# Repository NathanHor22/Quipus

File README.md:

# Quipus

Quipus records conversations with consent and turns them into a transcript,
meeting brief and follow-up tasks. Review proposed meetings in the dashboard
before sending Google Calendar invitations.

*Illustrative device render. The button diagram below defines the controls;
physical testing is still required for each new firmware build.*

[Open dashboard](https://quipus-sales-rep-assistant.vercel.app) ·
[Download firmware](https://github.com/NathanHor22/Quipus/actions/workflows/waveshare-firmware.yml) ·
[Full Waveshare guide](hardware/lantern-firmware/WAVESHARE.md) ·
[Developer setup](docs/configuration.md)

## Start with the recorder

This guide is for the **Waveshare ESP32-S3-LCD-1.54 non-touch board** with
16 MB flash and 8 MB PSRAM. Other supported boards need their own firmware.

1. Insert a **FAT32 microSD card** with the recorder powered off. Recording
   requires the card; setup and reports can work without it. Back up existing
   files before formatting a card. Quipus never formats cards automatically.
2. Connect USB-C power. For firmware **0.10.2**, open a successful
   [Waveshare firmware build](https://github.com/NathanHor22/Quipus/actions/workflows/waveshare-firmware.yml),
   download its `quipus-waveshare-lcd-154` artifact, extract it, then extract
   the firmware ZIP inside. Follow `README.txt` to flash all five images
   together. The manifest identifies the version, source commit and hashes.
3. In **Chrome on Windows or Android**, sign in at
   [Devices](https://quipus-sales-rep-assistant.vercel.app/dashboard/devices), choose
   **Connect with Bluetooth**, and select `Quipus-BT-XXXX`. Enter the LCD PIN
   if the operating system asks. Provide a **2.4 GHz Wi-Fi** network and choose
   **Save and connect**. Wait for this recorder to appear online in your account.
4. On **iPhone/Safari**, create a pairing code in Devices and use the
   [Wi-Fi setup fallback](hardware/lantern-firmware/WAVESHARE.md#wi-fi-fallback-and-recording-controls).
   Bluetooth is used for setup on supported browsers; recordings upload over Wi-Fi.
5. When the screen says **READY**, tap the **left button** to request recording.
   Ask everyone for consent and follow the spoken/display prompt. Confirm the
   screen says **RECORDING** before relying on capture.
6. Tap **left** again to stop. Keep the recorder powered while it saves and
   uploads. Open the conversation in the dashboard to check its audio,
   transcript and brief. Review any proposed meeting before approving an invite.

## Which button is which?

**Face the screen with its text upright and the three buttons ABOVE it**, as
in the device photos. In this orientation, the left button is PLUS, the middle
is PWR, and the right is BOOT. Turn the device around and left/right will reverse.

| Position | Tap and release | Hold |
| --- | --- | --- |
| **Left — PLUS** | Request consent/start recording; stop recording; interrupt a report | **1.2 s** while ready: play the daily report. During recording: stop. |
| **Middle — PWR** | **Volume down** | **2 s** while ready: power off/sleep. Pending private recordings block shutdown. |
| **Right — BOOT** | **Volume up** | During USB connection: enter the flashing bootloader. Leave released for normal startup. |
| **Left + right together** | — | **3 s**: clear Wi-Fi/pairing. Unsynced private recordings block reset. |

Volume taps require **0.10.2 or later**. Each tap changes volume by 10 points;
`V80` in the top bar means 80%. Zero mutes the speaker, and 100 is the configured
maximum. It starts at 80 after every restart. Volume affects prompts, reports,
chimes and replay, including during report playback; microphone gain and
recorded audio stay unchanged. Reset chords and long holds do not change volume.

The wake phrase is **Computer**, followed by a command. Follow the consent
prompt before recording. Daily reports need a working paired cloud connection.

## Battery

USB-C power works without a battery. For portable use, ask for the original
Waveshare **3.7 V 1000 mAh rechargeable lithium battery** for this exact model,
with an **MX1.25 2-pin connector**. Confirm pack dimensions and wire polarity
with the supplier; capacity and a similar-looking plug alone do not establish fit.
Install the supplied insulating sheet between the battery and PCB.

The default firmware does not estimate battery percentage. If you install a
battery, [enable the battery option and rebuild](hardware/lantern-firmware/WAVESHARE.md#build-and-flash)
to display the voltage-based estimate. Do not flash another board's image.

Sources: [Waveshare product](https://www.waveshare.com/esp32-s3-lcd-1.54.htm),
[hardware documentation](https://docs.waveshare.com/ESP32-S3-Touch-LCD-1.54),
[assembly guide](https://docs.waveshare.com/ESP32-S3-Touch-LCD-1.54/Instructions-For-Use).

## Develop and maintain

```sh
npm ci
npm run dev
```

Use Node.js 22. Local development without Supabase opens a fictional sample;
production authentication and provider setup are documented in
[configuration](docs/configuration.md) and [deployment](docs/deployment.md).

| Area | Source |
| --- | --- |
| Dashboard and server routes | `app/`, `components/`, `lib/` |
| Waveshare firmware and GPIO mapping | `hardware/lantern-firmware/` |
| Portable firmware tests | `scripts/test-firmware-boards.py` |
| Database migrations | `supabase/migrations/` |
| Recording worker | `recording-worker/` |
| System contracts | [ARCHITECTURE.md](ARCHITECTURE.md) |

```sh
python3 scripts/test-firmware-boards.py
python3 hardware/lantern-firmware/generate-setup-portal.py --check
npm run typecheck
npm test
npm run build
```

Firmware builds run in GitHub Actions using ESP-IDF 5.2.3. Compilation and
portable tests do not establish radio pairing, audible output or recording
reliability on a physical device. Before using a new build in a meeting,
check consent/start/stop, both volume buttons, a recording over 60 seconds,
its replay duration, and recovery after loss of Wi-Fi.

Waveshare support incorporates [jinchuntan/quipus](https://github.com/jinchuntan/quipus)
at `1d92ce5`, alongside this repository's existing firmware repairs.
See [integration notes](docs/upstream-sync.md) for provenance and validation.

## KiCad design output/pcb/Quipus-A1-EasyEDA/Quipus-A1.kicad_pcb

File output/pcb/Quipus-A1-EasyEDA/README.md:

# Quipus A1 — physical EasyEDA import carrier

This directory defines the physical footprints and placement used to build the custom Quipus recorder PCB. The import package is in `output/pcb/Quipus-A1-EasyEDA/`; its principal files are `Quipus-A1.kicad_sch` and `Quipus-A1.kicad_pcb`. The native EasyEDA design must be checked after importing those files.

The carrier has a 65 × 105 mm, 1.6 mm thick, four-layer board, 144 electrical components, 92 canonical nets and four additional mounting-hole footprints. Its 31 distinct physical packages are included in `Quipus.pretty/`. The front includes a non-electrical screen-envelope guide and the user buttons. Rear connectors include the battery, speaker, digital-microphone expansion and microSD socket. USB-C is at the bottom; the card socket opens toward the right side when viewed from the front. Both embedded microphone packages are mounted on the rear and receive sound through actual 0.60 mm non-plated board holes.

## Files and authority

| File | Purpose |
| --- | --- |
| `footprints-power.json`, `footprints-controller.json`, `footprints-audio.json` | Per-reference physical package, physical pad mapping, source and footprint SHA-256 |
| `placement.json` | Applied component position, rotation, face and mechanical envelopes; parent-owned |
| `kicad_format.py` | Conversion of physical footprint geometry into the legacy PCB import format |
| `build_import.py` | Builds the PCB, flat self-contained schematic, footprint library, CSVs and ZIP from the canonical source netlist |
| `validate_footprints.py` | Independent source-net/pin coverage, footprint pad numbering and checksum checks |
| `validate_import.py` | Independent final-carrier electrical associations and geometry-conversion audit |
| `validate_placement.py` | Independent actual-board physical placement audit |
| `render_placement.py` | Renders actual PCB pads, drilled holes, fabrication outlines, board edge and keepouts into a labelled front/rear PNG |
| `mic-placement-patch.json` | A four-part lower-microphone proposal against a recorded board hash; generating it does not change the PCB itself |

The circuit JSONs and `output/pcb/Quipus-A1/connections.json` establish electrical connections. A placement change does not alter their pin numbers or nets. The generated board is the authority for the preview; its SHA-256 appears in the preview and validation reports. Rear preview geometry is mirrored so it is a component-side view. The screen rectangle is a mounting guide for an off-board display, not an invented populated PCB component.

## Local checks

Run from the repository root with Python. Pillow is needed only for the PNG renderer.

```powershell
python hardware/quipus-pcb/rev-a/easyeda/validate_footprints.py
python hardware/quipus-pcb/rev-a/easyeda/build_import.py
python hardware/quipus-pcb/rev-a/easyeda/validate_import.py
python hardware/quipus-pcb/rev-a/easyeda/validate_placement.py
python hardware/quipus-pcb/rev-a/easyeda/render_placement.py
```

`build_import.py` rewrites generated import outputs using the current applied `placement.json`. It does not apply a proposal file. The independent audits and preview must be rerun after rebuilding, and the import ZIP must be refreshed after any file included in it changes.

The footprint audit checks the exact pad numbers against each circuit reference, including shared/repeated copper pads and unnumbered mechanical pads. The carrier audit compares the final schematic and PCB with canonical source pins/nets, checks every imported copper pad and graphic primitive, and tests the microphone annuli/paste, exposed pads, SD detector contacts and RF keepouts. The placement audit uses actual stitched courtyard polygons; it also checks front/back plated-through-hole interference, copper-to-edge clearance, mounting-head space, screen interference, connector direction and RF component exclusion on all four copper layers. Pad outlines in the geometric placement test use conservative rotated rectangles; circular mounting keepouts use 48-segment polygons.

Read `output/pcb/Quipus-A1-EasyEDA/import-validation.json` and `placement-validation.json` in this directory for the latest board hash and check results. Local checks do not exercise the native EasyEDA importer or native CAD rule engines.

## Verification status

| Stage | Status |
| --- | --- |
| Physical package/pad mapping and source comparison | Locally audited; details in the three footprint-review documents and `footprint-crosscheck.md` |
| Final carrier pin/net association and converted geometry | Local audit available in `import-validation.json` |
| Applied PCB physical placement | Local audit available in `placement-validation.json` |
| Native EasyEDA import and comparison of rendered package geometry | Imported; corrected microphone ground annuli accepted and saved in the native library, refreshed on U20/U21, with all eight quarter pads connected to GND |
| Native EasyEDA electrical-rule check (ERC) | Nine organized A3 schematic pages: 0 fatal findings, 0 errors, 0 warnings, 9 informational findings |
| Copper routing and ground pours | **Not complete** |
| Native PCB design-rule check (DRC) | Final native run: 451 unrouted connection findings, one schematic import metadata mismatch, **0 clearance findings**; routing remains incomplete |
| Fabrication release | **Not approved; this is an unrouted engineering carrier** |

Native cloud project: **Quipus A1 – Hardware Rev A**, ID `522f339b1e454ea3a6b4b8e11788511f`, PCB document `52caa9452ee66dee`; review date 1 October 2026. The nine schematic pages are ordered by function: USB-C/charger, USB current/suspend, power switch/always-on supply, main regulator, fuel gauge, processor/display/SD, controller support, buttons/service, and microphones/speaker. Native page sources retain all 144 references, 92 nets and 471 symbol pins. The final schematic-to-PCB import preview filtered for net changes contains no rows; the preview was cancelled because device metadata and the four PCB-only mounting holes still need deliberate synchronization. Evidence is in `native/`. A successful local audit or a visually plausible placement is not a routing or manufacturing sign-off.

The generated KiCad carrier and its ZIP do **not** incorporate the separate native microphone correction. Future reimports must preserve or reapply `native/microphone-footprint-final.esource` and verify all four pad-5 ground quarters on each microphone. The accepted native source checksum and native DRC evidence are separate from the generated-carrier checksum.

The current CAD-derived PNG and local placement report refer to PCB SHA-256 `5f48361c2ff1a57b59c6621943f8e72196b9cb33372bc079969b886fc56f1d6c`. Its top and bottom microphone ports are at (5.75,9.49) and (59.25,92.29) mm respectively. The lower bypass/series group has been applied; proposal files remain a record of the earlier geometry check, not the authority for the generated board. All 65 revised component positions/rotations/faces were also checked in native PCB Properties. The layout places charger/current-limit parts together on the lower front, the battery connectors toward the rear left, and the compact converter/distribution group on the lower rear. These groupings aid subsequent routing; zero placement collisions do not prove signal integrity or thermal performance.

## Specific native and assembly checks

After import, inspect the two Infineon microphone land patterns at high zoom: pin 5 is a copper annulus with an empty centre, the sound aperture is 0.60 mm NPTH, and its three paste sectors must remain separate. The native annulus uses four touching polygon pads, all numbered 5 and all assigned GND. Confirm the ESP32-S3 antenna notch and RF exclusion remain on all four copper layers; compare all USB-C shared contacts, the BQ27441 exposed-pad geometry, the MAX98357A exposed pad and the Hirose card detector pads against the source footprint files. Then use the actual native rules and the PCB fabricator's published tolerances for routing and final checks.

The microphone copper-to-sound-hole edge separation is 0.1925 mm and needs confirmation with the intended fabricator. Microphone stencil apertures and acoustic hole cleanliness need assembler review. The case must preserve both acoustic paths and microSD insertion/ejection clearance, and it must leave USB-C accessible. An external LiPo pouch, case rib or speaker chamber must not cover a microphone sound port. Do not fabricate from the preview image; fabrication output must come from the completed, checked native board.

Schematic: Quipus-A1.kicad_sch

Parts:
C1: 4.7uF 16V X7R; C_0805_2012Metric
C2, C16: 10uF 10V X7R; C_0805_2012Metric
C3, C17, C18: 22uF 10V X7R; C_0805_2012Metric
C4, C7, C8, C9, C10, C11, C12, C19: 100nF 10V; C_0603_1608Metric
C5, C6, C14, C20: 1uF 10V X7R; C_0603_1608Metric
C13: 1uF 10V lowleakage X7R; C_0805_2012Metric
C15: 10nF 25V X7R; C_0603_1608Metric
C21: 470nF 6.3V X7R; C_0603_1608Metric
C200, C202: 1uF X7R 10V; C_0603_1608Metric
C201, C203, C205: 100nF X7R 10V; C_0603_1608Metric
C204: 4.7uF X7R 10V; C_0603_1608Metric
C206: 10uF X7R 10V; C_0805_2012Metric
C207: 47uF X7R 10V DNP; C_1210_3225Metric; not fitted
C300: 1uF; C_0603_1608Metric
C301, C305, C310: 10uF; C_0603_1608Metric
C302, C306, C311, C320, C321, C330, C340: 100nF; C_0603_1608Metric
C303, C304: DNP / C0G tuning footprint; C_0603_1608Metric; not fitted
C312, C331, C332, C333, C334: 10nF; C_0603_1608Metric
D1: TPD1E10B06DYAR; Quipus_TI_DYA0002A_TPD1E10B06
F1: Littelfuse 0467002.NRHF 2 A; Fuse_0603_1608Metric
J1: GCT USB4105-GF-A; Quipus_GCT_USB4105_GF_A_SHARED_CONTACTS
J2: JST S2B-PH-SM4-TB(LF)(SN) battery; JST_PH_S2B-PH-SM4-TB_1x02-1MP_P2.00mm_Horizontal
J3: 3-pin keyed NTC connector - JST SH family candida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; JST_SH_SM03B-SRSS-TB_1x03-1MP_P1.00mm_Horizontal
J4: SM04B-SRSS-TB; JST_SH_SM04B-SRSS-TB_1x04-1MP_P1.00mm_Horizontal
J5: SM02B-SRSS-TB; JST_SH_SM02B-SRSS-TB_1x02-1MP_P1.00mm_Horizontal
J6: DM3AT-SF-PEJM5; Quipus_Hirose_DM3AT-SF-PEJM5_AB
J7: B8B-PH-K-S(LF)(SN); JST_PH_B8B-PH-K_1x08_P2.00mm_Vertical
L1: 0.47uH Coilcraft XFL4015-471ME; Quipus_Coilcraft_XFL4015
R1: 1.24k 1%; R_0603_1608Metric
R2: 2.00k 1%; R_0603_1608Metric
R3: 68.0k 1%; R_0603_1608Metric
R4, R5, R8, R9, R10, R11, R12, R14, R18, R316: 100k; R_0603_1608Metric
R6: 887k 1%; R_0603_1608Metric
R7, R13, R20, R21, R22, R25, R300, R301, R304, R305, R310, R311, R312, R313, R314, R321: 10k; R_0603_1608Metric
R15: 100ohm; R_0603_1608Metric
R16: 511k 1%; R_0603_1608Metric
R17: 91.0k 1%; R_0603_1608Metric
R19: 0.010ohm 1% lowTCR 0.25W; R_0805_2012Metric
R23, R24, R26: 1M; R_0603_1608Metric
R201, R202: 100 ohm 1%; R_0603_1608Metric
R203, R205, R207, R210, R211: 33 ohm 1%; R_0603_1608Metric
R204: 0 ohm; R_0603_1608Metric
R206, R208, R209: 100k 1%; R_0603_1608Metric
R302, R303, R315: 22ohm; R_0603_1608Metric
R306, R307: 33ohm; R_0603_1608Metric
R320: 330ohm; R_0603_1608Metric
R330, R331, R332, R333: 47k; R_0603_1608Metric
R341, R342: 49.9ohm; R_0603_1608Metric
SW1: POWER momentary normally-open; SW_SPST_B3U-1000P
SW300, SW301, SW302, SW303, SW304, SW305: B3U-1000P; Quipus_Omron_B3U-1000P
U1: ESP32-S3-WROOM-1-N16R8; ESP32-S3-WROOM-1
U2: BQ24074RGTR; Quipus_TI_RGT0016C_BQ24074
U3: TUSB320LAIRWBR; Quipus_TI_RWB0012A_TUSB320LAI
U4: TLV75533PDBVR; SOT-23-5
U5: SN74LVC1G04DBVR; SOT-23-5
U6: SN74LVC1G08DBVR; SOT-23-5
U7, U8: SN74LVC1G32DBVR; SOT-23-5
U9: LTC2951ITS8-1#TRPBF; TSOT-23-8
U10: TPS22918DBVR; SOT-23-6
U11: TPS63802DLAR; Quipus_TI_DLA0010A_TPS63802
U12: BQ27441DRZR-G1A; Quipus_TI_DRZ0012A_BQ27441
U13, U35: TPD2EUSB30DRTR; Texas_DRT-3
U20, U21: IM69D128SV01XTMA1; Infineon_IM69D128SV01_PG-TLGA-5-2_2.65x3.50mm_NPTH0.60
U22: MAX98357AETE+; MAX98357AETE_T1633-4_3x3mm_P0.5_EP1.23_90-0031C
U30: RV-3028-C7-TA-QC; MicroCrystal_C7_SON-8_1.5x3.2mm_P0.9mm
U31: PCA9536DR; SOIC-8_3.9x4.9mm_P1.27mm
U34: TS3USB221ARSER; Texas_UQFN-10_1.5x2mm_P0.5mm

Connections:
3V3_AON: C4.1, C6.1, C7.1, C8.1, C9.1, C10.1, R7.2, U3.12 (VDD), U4.5 (OUT), U5.5 (VCC), U6.5 (VCC), U7.5 (VCC), U8.5 (VCC)
3V3_FB: R16.2, R17.1, U11.4 (FB)
3V3_PG: R18.1, U11.5 (PG)
3V3_SYS: C17.1, C18.1, C19.1, C301.1, C302.1, C305.1, C306.1, C310.1, C311.1, C320.1, C330.1, C340.1, J6.4 (VDD), J7.8 (VCC), R4.2, R5.2, R13.2, R14.2, R16.1, R18.2, R21.2, R22.2, R25.2, R204.1, R300.1, R301.1, R304.1, R305.1, R310.1, R311.1, R312.1, R313.1, R314.1, R316.1, R330.1, R331.1, R332.1, R333.1, U1.2 (3V3), U11.6 (VOUT), U30.7 (VDD), U31.8 (VCC), U34.10 (VCC)
AMP_ENABLE: R209.1, U1.10 (GPIO17), U22.4 (SD_MODE)
AMP_GAIN: R208.2, U22.2 (GAIN_SLOT)
BAT_NTC: J3.1 (NTC), U2.1 (TS)
BAT_P: C2.1, R19.2, R320.1, U2.2 (BAT), U2.3 (BAT), U12.7 (SRN)
BAT_PACK_P: C20.1, J2.1 (PACK+), R19.1, U12.6 (BAT), U12.8 (SRP)
BOOT_N: R301.2, SW300.1 (A), U1.27 (GPIO0)
BTN_DOWN_N: C334.1, R333.2, SW304.1 (A), U31.5 (P3)
BTN_START_N: C331.1, R330.2, SW301.1 (A), U1.7 (GPIO7)
BTN_STOP_N: C332.1, R331.2, SW302.1 (A), U31.2 (P1)
BTN_UP_N: C333.1, R332.2, SW303.1 (A), U31.3 (P2)
BUCK_L1: L1.1, U11.9 (L1)
BUCK_L2: L1.2, U11.7 (L2)
CC_DEFAULT_NHIGH: R7.1, U3.7 (OUT1), U5.2 (A), U6.2 (B)
CHARGING_N: R4.1, U1.24 (GPIO47), U2.9 (CHG_N)
CHG_EN1: R10.1, U2.6 (EN1), U7.4 (Y)
CHG_EN2: R11.1, U2.5 (EN2), U8.4 (Y)
CHG_ILIM: R1.1, U2.12 (ILIM)
CHG_ISET: R2.1, U2.16 (ISET)
CHG_TMR: R3.1, U2.14 (TMR)
ESP_EN: C300.1, R300.2, SW305.1 (A), U1.3 (EN)
ESP_USB_DM: C303.1, R302.2, U1.13 (GPIO19_USB_D-)
ESP_USB_DP: C304.1, R303.2, U1.14 (GPIO20_USB_D+)
GAUGE_1V8: C21.1, U12.5 (VDD)
GAUGE_BIN: R20.1, U12.10 (BIN)
GAUGE_INT_N: R25.1, R26.1, U12.12 (GPOUT)
GND: C1.2, C2.2, C3.2, C4.2, C5.2, C6.2, C7.2, C8.2, C9.2, C10.2, C11.2, C12.2, C13.2, C14.2, C15.2, C16.2, C17.2, C18.2, C19.2, C20.2, C21.2, C200.2, C201.2, C202.2, C203.2, C204.2, C205.2, C206.2, C207.2, C300.2, C301.2, C302.2, C303.2, C304.2, C305.2, C306.2, C310.2, C311.2, C312.2, C320.2, C321.2, C330.2, C331.2, C332.2, C333.2, C334.2, C340.2, D1.2 (RETURN), J1.A1_B12 (GND), J1.B1_A12 (GND), J1.SH1 (SHIELD), J1.SH2 (SHIELD), J1.SH3 (SHIELD), J1.SH4 (SHIELD), J2.2 (PACK-), J3.2 (NTC_RETURN), J4.2 (GND), J6.6 (VSS), J6.B (CARD_DETECT_B), J6.SH (SHIELD), J7.7 (GND), R1.2, R2.2, R3.2, R8.2, R9.2, R10.2, R11.2, R17.2, R20.2, R23.2, R24.2, R26.2, R206.2, R209.2, R321.2, R341.2, R342.2, SW1.2, SW300.2 (B), SW301.2 (B), SW302.2 (B), SW303.2 (B), SW304.2 (B), SW305.2 (B), U1.1 (GND), U1.40 (GND), U1.41 (GND_EP), U2.4 (CE_N), U2.8 (VSS), U2.17 (EP), U3.3 (PORT), U3.10 (GND), U3.11 (EN_N), U4.2 (GND), U5.3 (GND), U6.3 (GND), U7.3 (GND), U8.3 (GND), U9.4 (GND), U10.2 (GND), U11.2 (MODE), U11.3 (AGND), U11.8 (GND), U12.3 (VSS), U12.13 (EP), U13.3 (GND), U20.4 (LR), U20.5 (GND), U21.5 (GND), U22.3 (GND), U22.11 (GND), U22.15 (GND), U22.17 (EP), U30.5 (VSS), U31.4 (GND), U34.5 (GND), U34.6 (OE_N), U34.9 (S), U35.3 (GND)
I2C_SCL: R22.1, R24.1, U1.17 (GPIO9), U12.2 (SCL), U30.3 (SCL), U31.6 (SCL)
I2C_SDA: R21.1, R23.1, U1.12 (GPIO8), U12.1 (SDA), U30.4 (SDA), U31.7 (SDA)
I2S1_BCLK: R211.1, U1.22 (GPIO14)
I2S1_BCLK_IC: R211.2, U22.16 (BCLK)
I2S1_DOUT: R207.1, U1.9 (GPIO16)
I2S1_DOUT_IC: R207.2, U22.1 (DIN)
I2S1_WS: R210.1, U1.8 (GPIO15)
I2S1_WS_IC: R210.2, U22.14 (LRCLK)
LCD_BL: J7.1 (BL), U1.21 (GPIO13)
LCD_CS_N: J7.4 (CS), R304.2, U1.18 (GPIO10)
LCD_DC: J7.3 (DC), U1.37 (GPIO43_U0TXD)
LCD_MOSI: J7.6 (DIN), R307.2
LCD_MOSI_MCU: R307.1, U1.19 (GPIO11)
LCD_RST_N: J7.2 (RST), R305.2, U1.36 (GPIO44_U0RXD)
LCD_SCLK: J7.5 (CLK), R306.2
LCD_SCLK_MCU: R306.1, U1.20 (GPIO12)
MAIN_RAW: C16.1, C205.1, C206.1, C207.1, R15.2, R208.1, U10.6 (VOUT), U11.1 (EN), U11.10 (VIN), U22.7 (VDD), U22.8 (VDD)
MIC_3V3: C200.1, C201.1, C202.1, C203.1, C204.1, J4.1 (3V3), R204.2, U20.1 (VDD), U21.1 (VDD), U21.4 (LR)
PDM_CLK: R203.1, R205.1, U1.4 (GPIO4)
PDM_CLK_EXT: J4.3 (CLK), R205.2
PDM_CLK_LOCAL: R203.2, U20.2 (CLOCK), U21.2 (CLOCK)
PDM_DIN0: R201.2, R202.2, U1.5 (GPIO5)
PDM_DIN1: J4.4 (DATA), R206.1, U1.6 (GPIO6)
POWER_HOLD: R14.1, U1.23 (GPIO21), U9.8 (KILL)
PWR_BUTTON_N: SW1.1, U9.2 (PB_N)
PWR_INT_N: R13.1, U1.11 (GPIO18), U9.5 (INT_N)
PWR_KILLT: C13.1, U9.3 (KILLT)
PWR_OFFT: C12.1, U9.7 (OFFT)
RTC_EVI: R321.1, U30.8 (EVI)
RTC_VBACKUP: C321.1, R320.2, U30.6 (VBACKUP)
SD_CD_N: C312.1, J6.A (CARD_DETECT_A), R316.2, U1.34 (GPIO41)
SD_CLK: J6.5 (CLK), R315.2
SD_CLK_MCU: R315.1, U1.31 (GPIO38)
SD_CMD: J6.3 (CMD), R310.2, U1.32 (GPIO39)
SD_D0: J6.7 (DAT0), R311.2, U1.33 (GPIO40)
SD_D1_PU: J6.8 (DAT1), R312.2
SD_D2_PU: J6.1 (DAT2), R313.2
SD_D3_PU: J6.2 (CD_DAT3), R314.2
SPK_N: J5.2 (SPK-), U22.10 (OUTN)
SPK_P: J5.1 (SPK+), U22.9 (OUTP)
SYS_ENABLE: R12.1, U9.6 (EN), U10.3 (ON)
SYS_QOD: R15.1, U10.5 (QOD)
SYS_RAMP_CT: C15.1, U10.4 (CT)
SYS_RAW: C3.1, C5.1, C11.1, C14.1, R12.2, U2.10 (OUT), U2.11 (OUT), U4.1 (IN), U4.3 (EN), U9.1 (VIN), U10.1 (VIN)
U20_D: R201.1, U20.3 (DATA)
U21_D: R202.1, U21.3 (DATA)
USB_CC1: J1.A5 (CC1), U3.1 (CC1), U13.1 (IO1)
USB_CC2: J1.B5 (CC2), U3.2 (CC2), U13.2 (IO2)
USB_DEFAULT_500: U6.4 (Y), U7.2 (B)
USB_DM: J1.A7 (D-1), J1.B7 (D-2), U34.7 (D-), U35.2 (D-)
USB_DM_ISO: R302.1, U34.2 (1D-)
USB_DP: J1.A6 (D+1), J1.B6 (D+2), U34.8 (D+), U35.1 (D+)
USB_DP_ISO: R303.1, U34.1 (1D+)
USB_ENUM_500: R8.1, U1.39 (GPIO1), U6.1 (A)
USB_HIGH_CURRENT_OK: U5.4 (Y), U8.2 (B)
USB_PGOOD_N: R5.1, U1.25 (GPIO48), U2.7 (PGOOD_N)
USB_PROTECTED: C1.1, D1.1 (IO), F1.2, U2.13 (IN)
USB_SUSPEND: R9.1, U1.38 (GPIO2), U7.1 (A), U8.1 (A)
USB_UNUSED_DM: R342.1, U34.4 (2D-)
USB_UNUSED_DP: R341.1, U34.3 (2D+)
USB_VBUS_DET: R6.2, U3.4 (VBUS_DET)
VBUS_5V: F1.1, J1.A4_B9 (VBUS), J1.B4_A9 (VBUS), R6.1

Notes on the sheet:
MATCHING GLOBAL LABELS ARE ELECTRICALLY CONNECTED / PHYSICAL PIN NUMBERS SHOWN

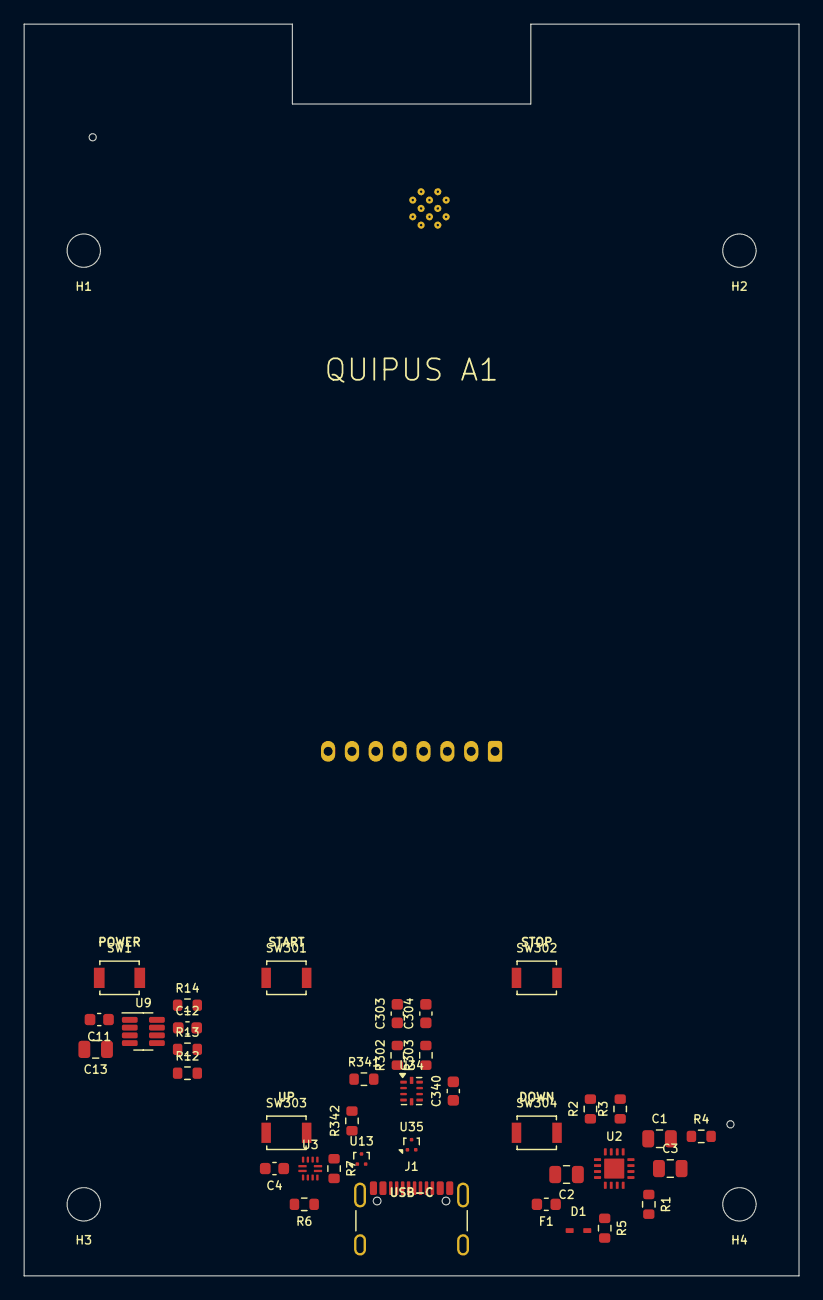
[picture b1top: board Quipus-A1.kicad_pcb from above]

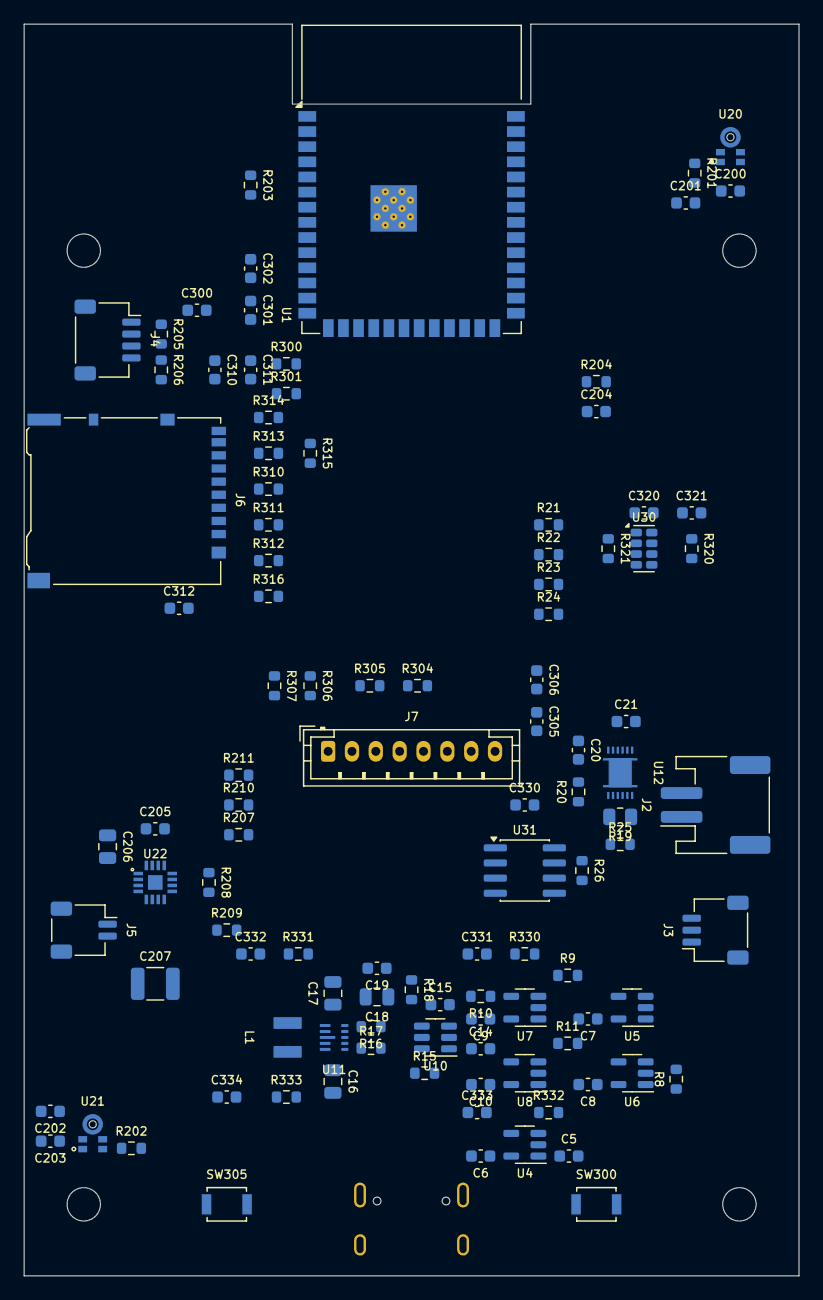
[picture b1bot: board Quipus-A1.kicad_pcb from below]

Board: 4 copper layers, 65.0 x 105.0 mm, 148 parts (106 on the bottom side), 92 nets, no tracks yet.

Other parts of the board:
H1, H2, H3, H4: MountingHole_2.8mm

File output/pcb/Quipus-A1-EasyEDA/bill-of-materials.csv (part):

Reference,Part/value,Package,Notes,Manufacturer reference
J1,GCT USB4105-GF-A,"GCT USB4105 PCB-top-mount USB2 receptacle, 0.95 mm shell stakes","Sixteen mating contacts map to twelve solder tails: A1/B12, A4/B9, B4/A9, B1/A12 share pads. Four shield stakes connect to ground. Pad names below explicitly combine shared contacts; verify the imported CAD footprint uses the same mapping. No external CC Rd resistors.",https://gct.co/files/drawings/usb4105.pdf
F1,Littelfuse 0467002.NRHF 2 A,0603 fuse,"Candidate fast-acting input fuse; verify current and temperature derating, inrush, and fault coordination on the PCB. The charger, not this fuse, controls USB current entitlement.",https://www.littelfuse.com/assetdocs/fuse-467-datasheet?asse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
U2,BQ24074RGTR,VQFN16 RGT0016 + exposed pad,Standard 4.2 V Li-ion chemistry. Temperature sensing must match the actual cell. ITERM intentionally unconnected for default termination.,https://www.ti.com/lit/ds/symlink/bq24074.pdf
R1,1.24k 1%,0603,,
R2,2.00k 1%,0603,,
R3,68.0k 1%,0603,,
R4,100k,0603,,
R5,100k,0603,,
C1,4.7uF 16V X7R,0805,,
C2,10uF 10V X7R,0805,,
C3,22uF 10V X7R,0805,,
J2,JST S2B-PH-SM4-TB(LF)(SN) battery,JST PH 2mm 2-position right angle SMT,"Board-defined pin 1 is positive. Verify pack polarity physically. Protected 1S 2000 mAh pack, standard 4.2 V charge, at least 2 A discharge capability. Swap with device off and USB unplugged.",https://www.jst-mfg.com/product/pdf/eng/ePH.pdf
J3,3-pin keyed NTC connector - JST SH family candidate,1mm SH 3pin exact drawing pending,Three positions prevent swapping with the two-position speaker connector. A 10 kOhm 103AT-2 thermistor must be thermally attached to the cell. Do not populate a fixed bypass resistor.,https://www.ti.com/lit/ds/symlink/bq24074.pdf
U3,TUSB320LAIRWBR,X2QFN12 RWB 1.6x1.6mm,Sink only; ADDR floating selects GPIO mode. OUT1 high means default current; low means 1.5 A or 3 A advertised. No external CC pull-down resistors.,https://www.ti.com/lit/ds/symlink/tusb320lai.pdf
R6,887k 1%,0603,,
R7,10k,0603,,
C4,100nF 10V,0603,,
U4,TLV75533PDBVR,SOT23-5 DBV,"Always-on control LDO, nominal 3.3 V on USB. At low battery it follows SYS_RAW minus dropout. Device off does not mean zero battery current.",https://www.ti.com/lit/ds/symlink/tlv755p.pdf
C5,1uF 10V X7R,0603,,
C6,1uF 10V X7R,0603,,
U5,SN74LVC1G04DBVR,SOT23-5 DBV,Y=!OUT1,https://www.ti.com/document-viewer/SN74LVC1G04/datasheet/GUI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
U6,SN74LVC1G08DBVR,SOT23-5 DBV,Y=USB_ENUM_500 AND OUT1,https://www.ti.com/lit/ds/symlink/sn74lvc1g08.pdf
U7,SN74LVC1G32DBVR,SOT23-5 DBV,EN1=SUSPEND OR (ENUM500 AND OUT1),https://www.ti.com/lit/ds/symlink/sn74lvc1g32.pdf
U8,SN74LVC1G32DBVR,SOT23-5 DBV,EN2=SUSPEND OR NOT OUT1,https://www.ti.com/lit/ds/symlink/sn74lvc1g32.pdf
R8,100k,0603,,
R9,100k,0603,,
R10,100k,0603,,
R11,100k,0603,,
C7,100nF 10V,0603,,
C8,100nF 10V,0603,,
C9,100nF 10V,0603,,
C10,100nF 10V,0603,,
U9,LTC2951ITS8-1#TRPBF,TSOT23-8 TS8,Use the -1 variant with active-high enable. Pull KILL up to switched 3V3 so startup does not depend on firmware responding within 512 ms.,https://www.analog.com/media/en/technical-documentation/data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
SW1,POWER momentary normally-open,physical switch footprint pending,On press: at least 128 ms. Off request: nominal 674 ms hold. Forced off approximately 6.54 s after the shutdown interrupt.,
C11,100nF 10V,0603,,
C12,100nF 10V,0603,Nominal total off-button debounce approximately 674 ms.,
C13,1uF 10V lowleakage X7R,0805,Nominal 6.54 s shutdown grace period after interrupt; verify capacitance tolerance and timing on the bench.,
R12,100k,0603,,
R13,10k,0603,,
R14,100k,0603,,
U10,TPS22918DBVR,SOT23-6 DBV,Rated 2 A main load switch. Target normal system peak below 1.5 A at this node. Both amplifier and buck-boost supply are downstream. Do not inject external power into SYS_SW.,https://www.ti.com/lit/ds/symlink/tps22918.pdf
C14,1uF 10V X7R,0603,,
C15,10nF 25V X7R,0603,Slew approximately 5.53 ms/V; rise approximately 24 ms at 4.4 V. Verify loaded startup.,
R15,100ohm,0603,Limits output discharge current. QOD must not connect to an independently powered rail.,
U11,TPS63802DLAR,VSON/HotRod DLA10 1.4x2.3mm,MODE low selects power saving. The board cannot draw 2 A from 3V3 plus speaker power simultaneously through a 2 A battery connector.,https://www.ti.com/lit/ds/symlink/tps63802.pdf
L1,0.47uH Coilcraft XFL4015-471ME,Coilcraft XFL4015,Datasheet candidate: 5.4 A saturation current and 7.6 mOhm DCR. Verify exact supplier land pattern and available revision.,
R16,511k 1%,0603,,
R17,91.0k 1%,0603,,
R18,100k,0603,,
C16,10uF 10V X7R,0805,,
C17,22uF 10V X7R,0805,,
C18,22uF 10V X7R,0805,,
C19,100nF 10V,0603,,
U12,BQ27441DRZR-G1A,VSON12 DRZ0012A 2.5x4 mm + exposed pad,I2C address 0x55. This gauge does not replace cell protection. All charger and external battery loads connect downstream of R19. VDD must not supply other circuits.,https://www.ti.com/lit/ds/symlink/bq27441-g1.pdf
R19,0.010ohm 1% lowTCR 0.25W,0805 sense resistor,Kelvin sense from both resistor pads. At 2 A: 20 mV drop and 40 mW dissipation.,
R20,10k,0603,Defined for cold battery replacement; not automatic hot-swap insertion detection.,
R21,10k,0603,,
R22,10k,0603,,
R23,1M,0603,,
R24,1M,0603,,
R25,10k,0603,,
R26,1M,0603,Prevents a floating input with main power off. Local test net unless an MCU GPIO is assigned.,
C20,1uF 10V X7R,0603,,
C21,470nF 6.3V X7R,0603,,
U13,TPD2EUSB30DRTR,DRT 3-pin,"CC1/CC2 protection, close to USB connector. Verify transient clamping with layout.",https://www.ti.com/lit/ds/symlink/tpd2eusb30.pdf
D1,TPD1E10B06DYAR,DYA SOD-523,VBUS ESD clamp. Does not provide sustained overvoltage protection. Verify chosen package and protection coordination.,https://www.ti.com/lit/ds/symlink/tpd1e10b06.pdf
U1,ESP32-S3-WROOM-1-N16R8,"Espressif WROOM-1 18.0x25.5mm module, 40 castellated pads plus GND pad 41","Exact N16R8 ordering code only. GPIO35-37 are reserved for internal Octal PSRAM; leave disconnected. GPIO3/45/46 left unused. GPIO42 is spare; GPIO7 is Start/Enter and RTC-domain wake input. GPIO43 is UART0 TX at ROM boot: LCD_CS_N external pull-up prevents interpreting ROM transitions. Native USB is the service interface; LCD uses SPI2_HOST, not the flash SPI1 bus. GPIO47/48 are valid 3.3V for N16R8; do not silently substitute N16R16VA.",https://documentation.espressif.com/esp32-s3-wroom-1_wroom-1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
U30,RV-3028-C7-TA-QC,Micro Crystal C7 3.2x1.5x0.8mm,"I2C address 0x52. Factory-program EEPROM backup BSM=11 (LSM), TCE=0 and disable CLKOUT. Backup switchover is disabled on new parts; unconfigured part does not preserve time after main rail off. Backup uses protected BAT_P; no time guarantee if LiPo removed or protection trips. I2C pull-ups reside on switched 3V3 power sheet.",https://www.microcrystal.com/fileadmin/Media/Products/RTC/Ap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
U31,PCA9536DR,"TI D SOIC-8 4.9x3.91mm, 1.27mm pitch","I2C address 0x41. Stop/Back, Up and Down only; Start/Enter connects directly to RTC GPIO7. P0 is unused and held high by the expander internal weak pull-up; configure as input and mask out its reading. Configure 0x03=0x0F explicitly; input register 0x00; active-low switches. Poll approximately 10ms while UI is active, 20ms debounce; stop polling in deep sleep and use direct Start button to wake. Powered off with ESP. Hardware power/BOOT/RESET bypass expander.",https://www.ti.com/lit/ds/symlink/pca9536.pdf
U34,TS3USB221ARSER,TI RSE UQFN-10 2.0x1.5mm,Power-off-protected USB data switch. S=0/OE_N=0 selects port1 only while powered. Main-off VCC=0 has specified Ioff <=2uA per I/O (not zero). D+/D- remain isolated from unpowered ESP when USB charging remains active. Fit unused-port 49.9ohm terminations per manufacturer recommendation. Validate full-speed eye/edge waveform after adding switch plus series damping.,https://www.ti.com/lit/ds/symlink/ts3usb221a.pdf
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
